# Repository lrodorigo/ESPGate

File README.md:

<p align="right">🇬🇧 English · <a href="README_IT.md">🇮🇹 Italiano</a></p>

<h1 align="center">⛩️ ESPGate v1.0</h1>

<h2 align="center">⏳ Built to last 10 years.<br>Isolated. Surge-protected. Local-first.</h2>

<p align="center"><b>Native ESPHome / Home Assistant 230V AC Gate &amp; Roller Shutter Controller</b></p>

<p align="center">
  <br>
  
</p>

> 💡 *Install it once. Forget it. Your gate just works—through thunderstorms, power surges and a decade of daily cycles.*

* 🧠 **Platform:** Custom `150 × 110 mm` PCB built around an `ESP32-S3-WROOM-1` for native ESPHome integration.
* ⚙️ **Target Load:** Single-phase `230V AC` sliding/swing gates (**single or double leaf**) and garage roller shutters.
* 🛡️ **Design Goal:** Industrial-grade mains isolation and surge protection in a single self-contained board—zero external relay modules or floating power supplies.
* ⚙️ **Motors:** up to `2×` single-phase `230V AC` motors (open/close), one per leaf.
* 📥 **Inputs:** opto-isolated `24V` (photocells, limit switches, push-buttons) plus a `433.92 MHz` rolling-code RF receiver (`4` channels).
* 📤 **Outputs:** motor phase + direction relays, a neutral relay per leaf, `230V AC` flashing beacon (SSR) and a free-contact auxiliary relay (`AUX`).

---

## 🤔 Why Yet Another Gate Controller?

* ❌ **The DIY Problem:** Cobbling consumer DIN-rail Wi-Fi relays with external `24V` PSUs and shared grounds leads to ESP32 brownouts, welded relay contacts, or fried GPIOs after the first thunderstorm.
* 🔒 **The Commercial Problem:** Traditional gate boards handle high voltage well, but trap you in proprietary remotes or clunky cloud bridges.
* ✅ **The ESPGate Solution:** Full galvanic isolation, dedicated surge protection, and hardware-interlocked relays paired with local-first ESPHome firmware.

> ⚠️ **HIGH VOLTAGE SAFETY WARNING**
> * Operates directly on lethal **230V AC mains voltage**. Always disconnect power at the main breaker before wiring or servicing.
> * Open-hardware DIY project without commercial CE certification—intended for experienced makers or installation by qualified personnel inside an IP56/IP65 enclosure.

---

## 📌 Project Status

> ### 🙋 Looking for expenses split!
> Help me get the first `5` boards made: **3 spots available at ~`55–60 €` each.**

* 🧪 **Stage:** Design updated with **double-leaf support** and an **RF receiver** (see [Changelog](#-changelog)), **not ordered yet**. Some sections below (renders, terminals, architecture) may still describe the previous single-leaf revision.
* 📦 **Batch:** The first prototype batch (PCB + SMT assembly from JLCPCB, `5` boards) is ready in the cart and will be ordered as soon as the 3 spare boards find a home.
* 🤝 **Looking for 3 early adopters:** I keep `2` boards for myself and I'm looking for `3` people willing to refund the cost of the other three boards (about `55–60 €` per board). Spending ~`300 €` for just two boards makes no sense, so splitting the batch is what makes this prototype run viable.
* 🛡️ **Risk is mine:** I will personally perform the **first power-up** and bring-up of every board. If a board doesn't work, that's on me, not on you.
* 📬 **Interested?** Open an issue or get in touch.

---

## 📝 Changelog

### Unreleased (since v1.0)

* ➕ **Double-leaf gate support:**
  * The `AUX` `triac` output was replaced with a `relay`, and an extra `relay` + `optocoupler` were added to drive a second leaf.
  * Both leaves share the same `MOTOR DIR` relay, so they always move in the direction set by how the phase is wired: leaf 1 clockwise / leaf 2 counter-clockwise (standard), or leaf 1 clockwise / leaf 2 clockwise.
  * The delay between the two leaves is **programmable**.
  * The direction wires of the two motors are wired **in parallel** (phase), while each leaf has its **own neutral relay**: leaf 1 uses the dedicated neutral relay (`GPIO15`), leaf 2 uses the `AUX` relay (`GPIO5`) with `AUX COM` wired to `N`.
* 📡 **RF remote receiver:**
  * Added a [`433.92 MHz` 4-channel rolling-code receiver module](https://rf-modules.com/433-92-Receiver-Module-with-on-board-decoding-RC-RHCS-4CH-p244180431) with on-board decoding.
  * `SMA` connector on the PCB for an external antenna.
  * The `4` RF channels are wired to independent ESP32 GPIOs, not in parallel with the push-buttons.
* 📍 **Pinout:** updated to the current schematic.

---

## 🏗️ System Architecture

---

## ✨ Key Hardware Features

* 🧠 **MCU & Debug:** `ESP32-S3-WROOM-1` with `FLASH`, `RESET`, and `CONFIG` tactile buttons, onboard UART header (`TX`/`RX`), and `STATUS` LED.
* 🔋 **Isolated Power:** Dual isolated Mean Well `IRM` AC/DC modules separating the `24V` field domain from the `3.3V` logic domain.
* ⚙️ **230V AC Motor Drive (`MOTOR`):**
  * Hardware-interlocked `AgSnO2` power relays (`MOTOR PWR` + `MOTOR DIR`) for Open/Close control (`AP` / `CH` / `COM`).
  * RC snubber networks across relay contacts to suppress inductive motor arcing.
* 🚨 **230V AC Auxiliary Outputs (`LAMP` / `AUX`):**
  * Opto-isolated Solid-State Relay (`BC2223A` SSR) for the flashing beacon (`LAMPEGGIANTE`).
  * `AUX` relay output for an auxiliary load (courtesy light / electric lock) or, with `AUX COM` wired to `N`, as the neutral relay of leaf 2.
* 🛡️ **Protection & Creepage:**
  * Dedicated `5×20 mm` replaceable fuses: `FH1` on the power supplies input, `FH3` on the motors, `FH4` on the `+24V` supply of photocells and inputs.
  * `14D471K` Metal Oxide Varistors (`MOV`) on AC mains input and output stages.
  * Physical PCB milling slots (`Edge.Cuts`) between `230V AC` and low-voltage sections.
* 🔌 **6× Opto-Isolated 24V Field Inputs (`LTV-847S`):**
  * Galvanically isolated inputs with onboard diagnostic LEDs (`P1`, `P2`, `L1`, `L2`, `B1`, `B2`):
    * **Photocells (`PHOTOC`):** `P1`, `P2`
    * **Limit Switches (`LIMIT SW`):** `L1` (Open), `L2` (Close)
    * **Push-Buttons (`BUTTONS`):** `B1` (Step-by-Step / Open), `B2` (Close / Pedestrian)
  * Dedicated `+24V` output terminals (`+24V INPUTS`) to power photocells and dry-contact switches.
* 📦 **Enclosure Fit:** Fits inside a standard **Gewiss GW44207** (`190 × 140 × 70 mm`) IP56 junction box via a 3D-printed adapter plate.

---

## 🔩 Terminal Block Overview

* 🔌 **J1 (`AC IN`):** `230V AC 50Hz` mains input (`L`, `N`, `PE`) protected by `FH1` (power supplies input) + `MOV`.
* ⚙️ **J2 (`MOTOR`):** `230V AC` single-phase motor output (`COM`, `OPEN`, `CLOSE`, `PE`) with hardware interlock and snubbers.
* 🚨 **J3 (`LAMP / AUX`):** `230V AC` SSR output for the flashing beacon (`LAMP`) and `AUX` relay output (leaf 2 neutral when `AUX COM` is wired to `N`).
* 🔋 **J4 (`+24V INPUTS`):** Isolated `24V DC` sensor supply (`-`, `-`, `+24`, `+24`).
* 👁️ **J5 (`PHOTOC`):** Opto-isolated photocell inputs (`C`, `1`, `2` → `P1`, `P2`).
* 🛑 **J6 (`LIMIT SW`):** Opto-isolated open/close limit switch inputs (`C`, `1`, `2` → `L1`, `L2`).
* 🔘 **J7 (`BUTTONS`):** Opto-isolated wall push-button inputs (`C`, `1`, `2` → `B1`, `B2`).

---
## 📍 ESP32-S3 Pinout Map

* 📤 **Outputs:**
  * `GPIO16` (`ESP_REL_MOT_PWR`, Active `HIGH`): Motor phase activation relay (`MOTOR PWR`).
  * `GPIO7` (`ESP_REL_DIR`, Active `HIGH`): Direction relay (`MOTOR DIR`), shared by both leaves.
  * `GPIO15` (`ESP_N_MOT1`, Active `HIGH`): Neutral relay of motor 1 / leaf 1.
  * `GPIO6` (`ESP_LAMP`, Active `HIGH`): Flashing beacon SSR (`LAMP`).
  * `GPIO5` (`ESP_AUX`, Active `HIGH`): `AUX` relay, used as the neutral relay of leaf 2 when `AUX COM` is wired to `N`.
  * `GPIO4` (`ESP_LED_GR`, Active `HIGH`): Onboard green status LED (`STATUS`).
* 📥 **Inputs:**
  * `GPIO9` (`ESP_IN_FOTOC_1`, Active `LOW`): Photocell 1 (`P1`).
  * `GPIO10` (`ESP_IN_FOTOC_2`, Active `LOW`): Photocell 2 (`P2`).
  * `GPIO12` (`ESP_IN_LIMIT_1`, Active `LOW`): Limit switch 1 (`L1`).
  * `GPIO11` (`ESP_IN_LIMIT_2`, Active `LOW`): Limit switch 2 (`L2`).
  * `GPIO38` (`ESP_IN_BTN_1`, Active `LOW`): Push-button 1 (`B1`).
  * `GPIO39` (`ESP_IN_BTN_2`, Active `LOW`): Push-button 2 (`B2`).
  * `GPIO13` (`SW3`, Active `LOW`): Onboard `CONFIG` button.
* 📡 **RF Receiver (`J9`, `4` independent channels, not in parallel with the buttons):**
  * `GPIO14` (`RF_CH1`), `GPIO21` (`RF_CH2`), `GPIO40` (`RF_CH3`), `GPIO41` (`RF_CH4`), each with a `10 kΩ` pull-up to `3.3V`.
* 🔌 **Debug UART (`J4`):**
  * `GPIO0` (`SW1`, Active `LOW`): Onboard `FLASH` / Boot mode button.
  * `GPIO43` (`TXD0`) / `GPIO44` (`RXD0`): 3.3V UART header (`330 Ω` series protection resistors).

---

## 🚀 Quick Start (ESPHome)

* **1. Flash:** Connect a `3.3V` USB-to-UART adapter to the `ESP` header (`+`, `-`, `RX`, `TX`), hold `FLASH`, and press `RESET`.
* **2. Configure:** Load the ESPHome YAML configuration, set `secrets.yaml` (Wi-Fi + API key), and tune `open_duration` / `close_duration`.
* **3. Bench Test:** Verify limit switches (`L1`, `L2`) and photocells (`P1`, `P2`) via onboard diagnostic LEDs before connecting `230V AC` motor leads.

---

## 📜 Disclaimer & License

* **License:** CERN Open Hardware Licence v2 - Permissive (`CERN-OHL-P`) / `MIT`.
* **Liability:** Provided as-is for educational and DIY purposes; the author assumes no liability for personal injury, property damage, or regulatory compliance.

---

## 📐 Mechanical

* 🔩 **Mounting:** Secured by `4×` **M4** screws, one in each corner.
* 📏 **Board Size:** `150 × 111 mm`, mounting holes on a `138 × 100 mm` grid.

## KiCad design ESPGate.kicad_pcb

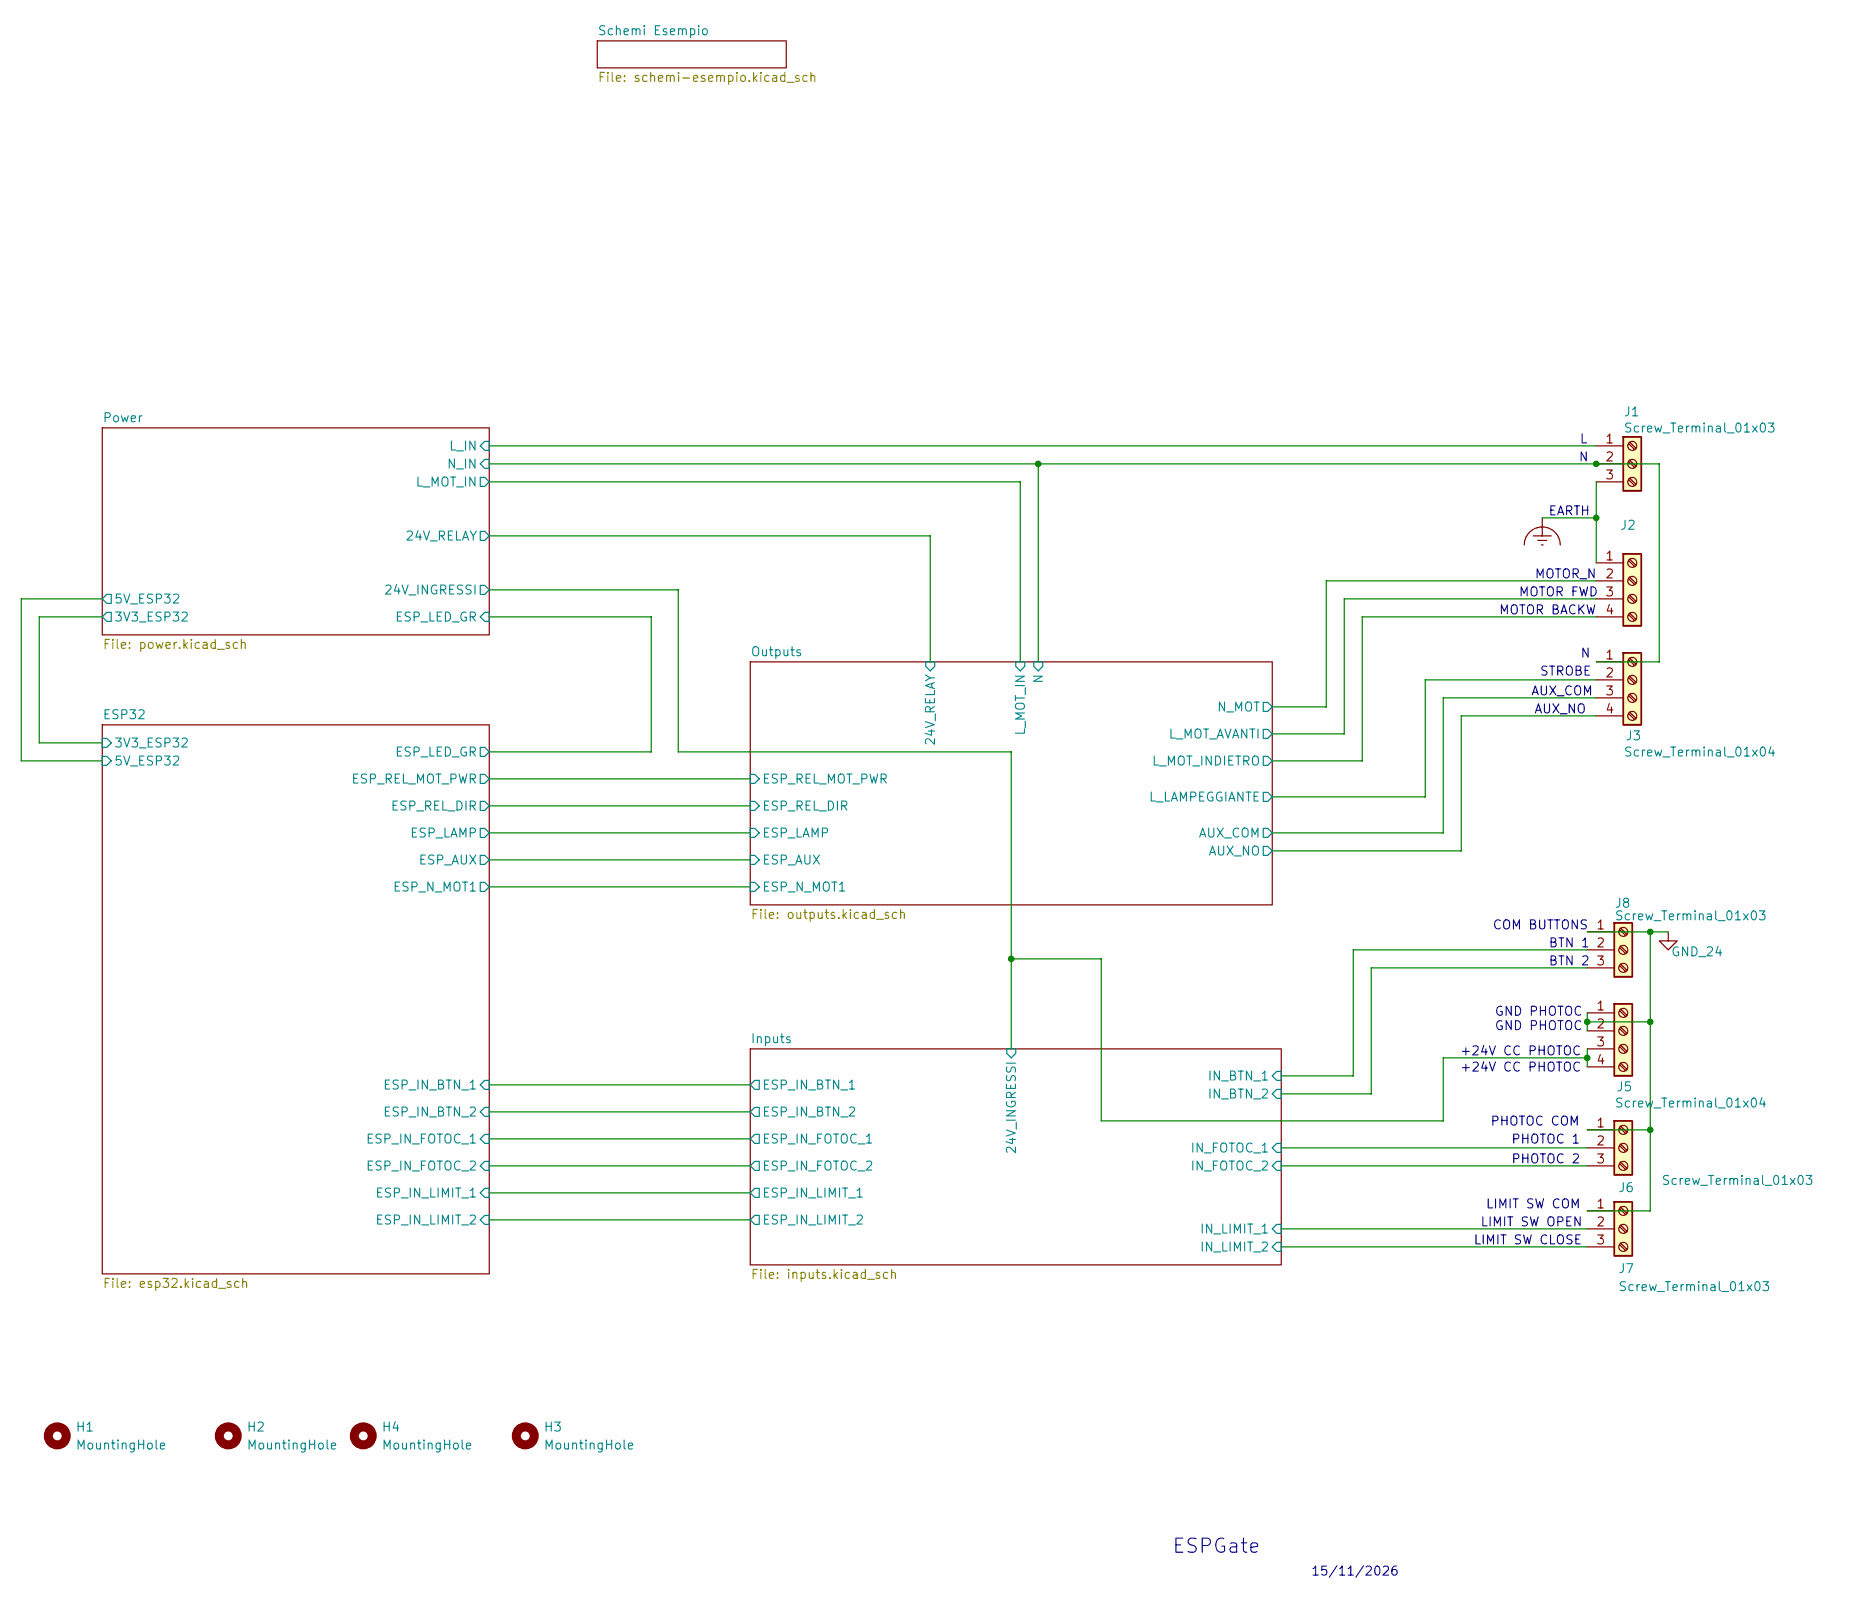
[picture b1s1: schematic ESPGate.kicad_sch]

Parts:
H1, H2, H3, H4: MountingHole; MountingHole_4.3mm_M4_DIN965
J1, J6, J7, J8: Screw_Terminal_01x03; CONN-TH_3P-P5.00_WJ500V-5.08-3P
J2, J3, J5: Screw_Terminal_01x04; CONN-TH_4P-P5.08_DIBO_DB128V-5.08

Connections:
24V_INGRESSI: J5.3, J5.4; also elsewhere on the board
/Inputs/IN_BTN_1: J8.2; also elsewhere on the board
/Inputs/IN_BTN_2: J8.3; also elsewhere on the board
/Inputs/IN_FOTOC_1: J6.2; also elsewhere on the board
/Inputs/IN_FOTOC_2: J6.3; also elsewhere on the board
/Inputs/IN_LIMIT_1: J7.2; also elsewhere on the board
/Inputs/IN_LIMIT_2: J7.3; also elsewhere on the board
/Outputs/AUX_COM: J3.3; also elsewhere on the board
/Outputs/AUX_NO: J3.4; also elsewhere on the board
/Outputs/L_LAMPEGGIANTE: J3.2; also elsewhere on the board
/Outputs/L_MOT_AVANTI: J2.3; also elsewhere on the board
/Outputs/L_MOT_INDIETRO: J2.4; also elsewhere on the board
/Outputs/N: J1.2, J3.1; also elsewhere on the board
/Outputs/N_MOT: J2.2; also elsewhere on the board
/Power/L_IN: J1.1; also elsewhere on the board
Earth_Clean: J1.3, J2.1
GND_24: J5.1, J5.2, J6.1, J7.1, J8.1; also elsewhere on the board

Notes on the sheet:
BTN 2
15/11/2026
+24V CC PHOTOC
AUX_NO
GND PHOTOC
PHOTOC COM
STROBE
ESPGate
LIMIT SW OPEN
LIMIT SW COM
PHOTOC 2
MOTOR BACKW
BTN 1
MOTOR_N
PHOTOC 1
EARTH
LIMIT SW CLOSE
MOTOR FWD
COM BUTTONS
AUX_COM

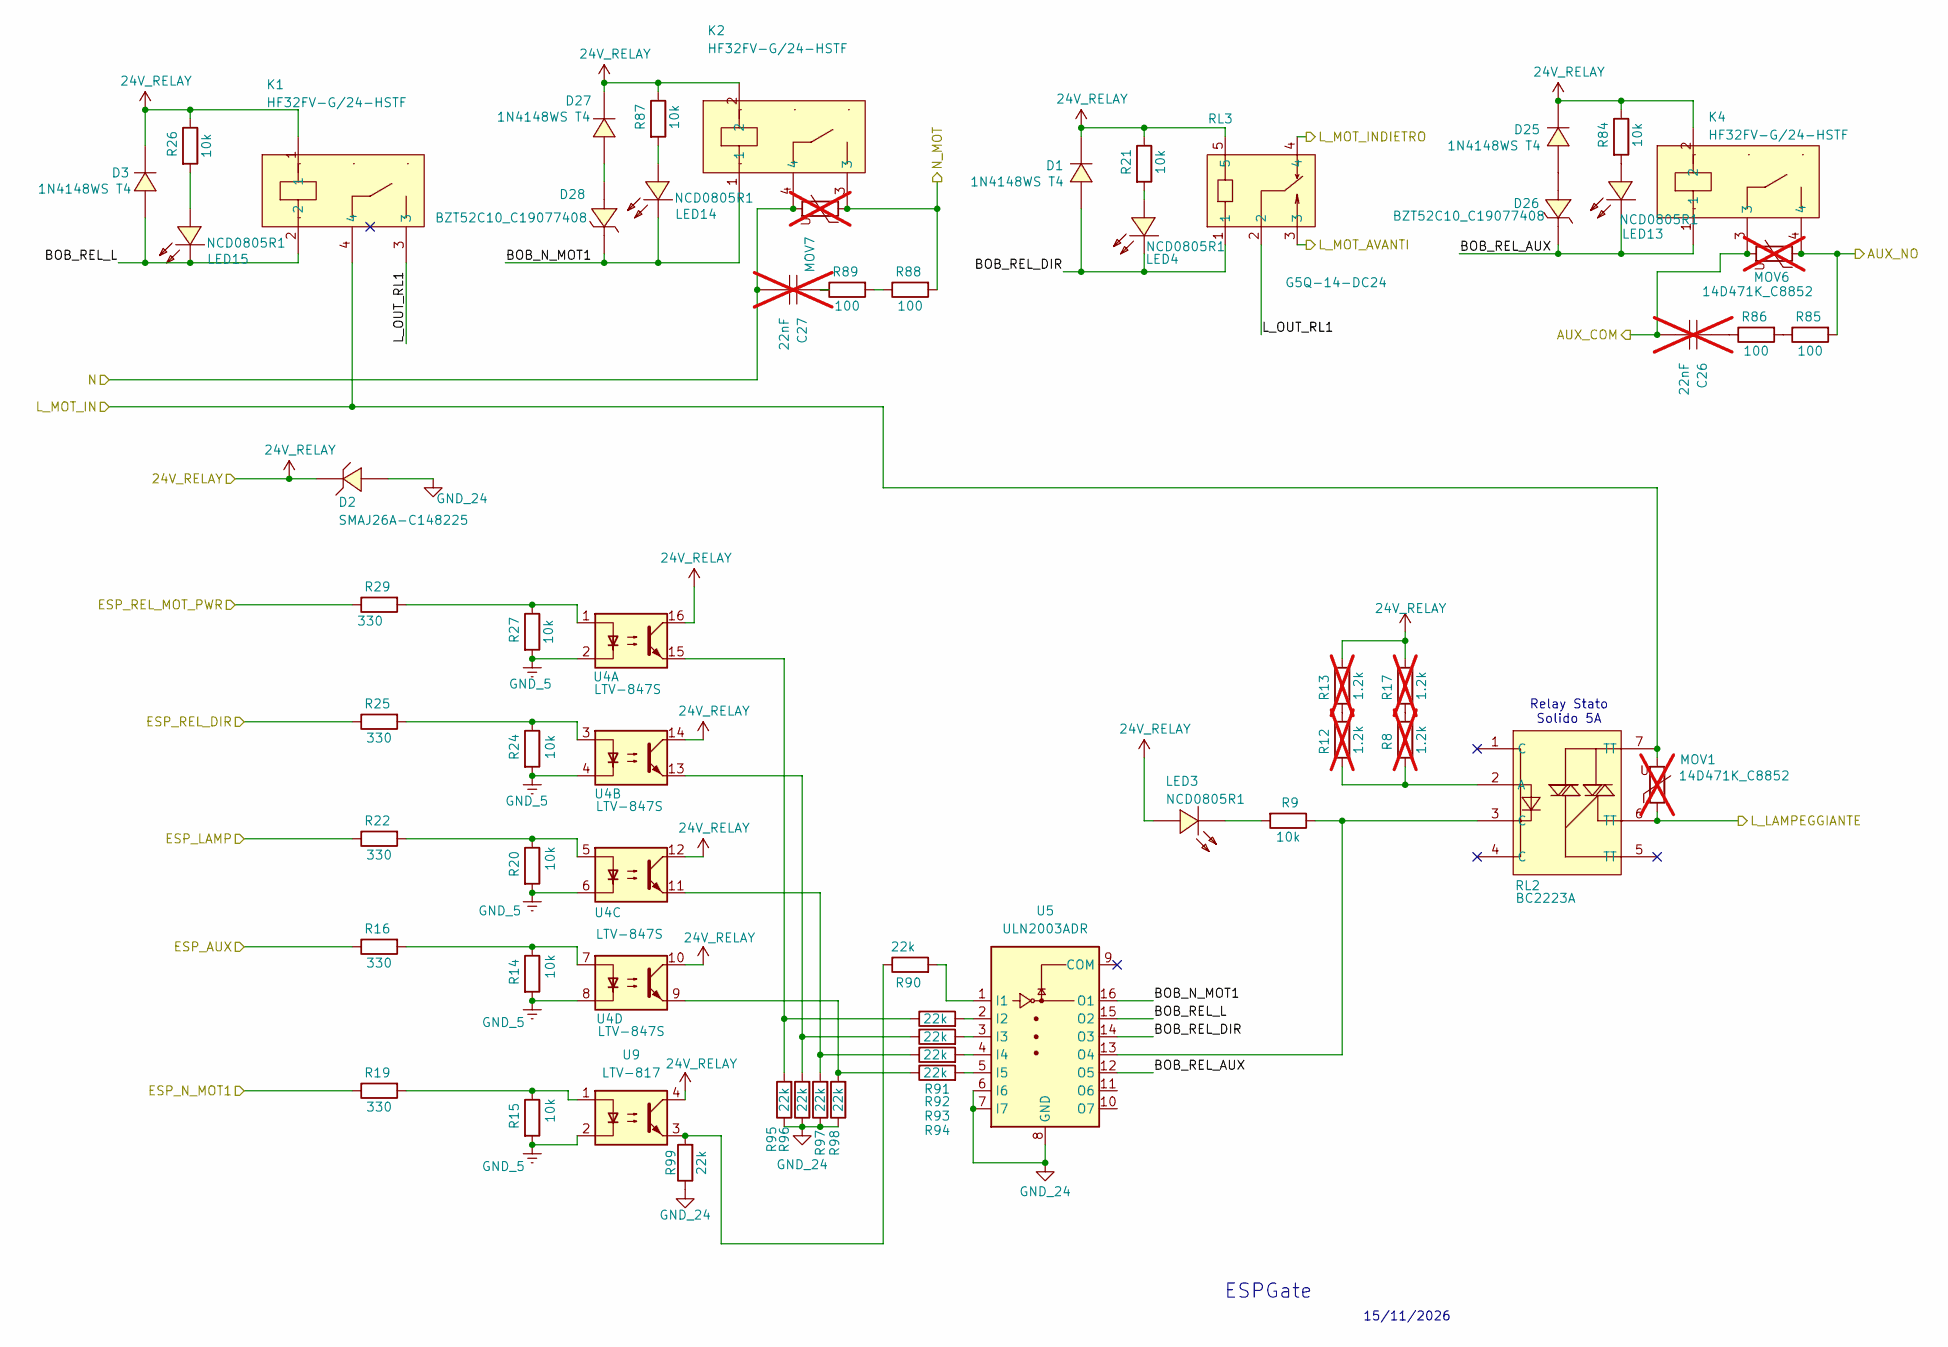
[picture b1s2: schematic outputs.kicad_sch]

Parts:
C26, C27: 22nF; CAP-TH_L13.0-W5.0-P10.00-D0.6; LCSC Part C390050; not fitted
D1, D3, D25, D27: 1N4148WS T4; SOD-323_L1.8-W1.3-LS2.5-RD; LCSC Part C2128
D2: SMAJ26A-C148225; SMA_L4.4-W2.6-LS5.0-RD; LCSC Part C148225
D26, D28: BZT52C10_C19077408; SOD-123_L2.7-W1.6-LS3.7-RD; LCSC Part C19077408
K1, K2, K4: HF32FV-G/24-HSTF; RELAY-TH_HF32FV-G; LCSC Part C194243
LED3, LED4, LED13, LED14, LED15: NCD0805R1; LED0805-R-RD; LCSC Part C84256
MOV1, MOV6, MOV7: 14D471K_C8852; RES-TH_L16.5-W5.9-P7.50-D0.8-S3.00; LCSC Part C8852; not fitted
R8, R12, R13, R17: 1.2k; R0805; LCSC Part C17379; not fitted
R9, R14, R15, R20, R21, R24, R26, R27, R84, R87: 10k; R0805; LCSC Part C17414
R16, R19, R22, R25, R29: 330; R0805; LCSC Part C17630
R85, R86, R88, R89: 100; R1206; LCSC Part C17901
R90, R91, R92, R93, R94, R95, R96, R97, R98, R99: 22k; R0603; LCSC Part C31850
RL2: BC2223A; SMD-8_7P-L9.7-W6.4-P2.54-LS10.0-BL; LCSC Part C596513
RL3: G5Q-14-DC24; RELAY-TH_G5Q-14-DCXX; LCSC Part C397242
U4: LTV-847S; SMDIP-16_W9.53mm; LCSC Part C114599
U5: ULN2003ADR; SOIC-16_L9.9-W3.9-P1.27-LS6.0-BL; LCSC Part C7512
U9: LTV-817; OPTO-SMD-4_L4.6-W6.5-P2.54-LS10.3-BL; LCSC Part C109227

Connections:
24V_RELAY: D1.1 (K), D2.1 (C), D3.1 (K), D25.1 (K), D27.1 (K), K1.1, K2.2, K4.2, LED3.1 (+), R13.2, R17.2, R21.1, R26.1, R84.1, R87.1, RL3.5, U4.10, U4.12, U4.14, U4.16, U9.4; also elsewhere on the board
/ESP32/ESP_AUX: R16.1; also elsewhere on the board
/ESP32/ESP_LAMP: R22.1; also elsewhere on the board
/ESP32/ESP_N_MOT1: R19.1; also elsewhere on the board
/ESP32/ESP_REL_DIR: R25.1; also elsewhere on the board
/ESP32/ESP_REL_MOT_PWR: R29.1; also elsewhere on the board
/Outputs/AUX_COM: C26.1, K4.3, MOV6.2; also elsewhere on the board
/Outputs/AUX_NO: K4.4, MOV6.1, R85.2; also elsewhere on the board
/Outputs/BOB_N_MOT1: D28.1 (K), K2.1, LED14.2 (-), U5.16 (O1)
/Outputs/BOB_REL_AUX: D26.1 (K), K4.1, LED13.2 (-), U5.12 (O5)
/Outputs/BOB_REL_DIR: D1.2 (A), LED4.2 (-), RL3.1, U5.14 (O3)
/Outputs/BOB_REL_L: D3.2 (A), K1.2, LED15.2 (-), U5.15 (O2)
/Outputs/L_LAMPEGGIANTE: MOV1.1, RL2.6 (TT); also elsewhere on the board
/Outputs/L_MOT_AVANTI: RL3.3; also elsewhere on the board
/Outputs/L_MOT_IN: K1.4, MOV1.2, RL2.7 (TT); also elsewhere on the board
/Outputs/L_MOT_INDIETRO: RL3.4; also elsewhere on the board
/Outputs/L_OUT_RL1: K1.3, RL3.2
/Outputs/N: C27.1, K2.4, MOV7.2; also elsewhere on the board
/Outputs/N_MOT: K2.3, MOV7.1, R88.2; also elsewhere on the board
GND_5: R14.2, R15.2, R20.2, R24.2, R27.2, U4.2, U4.4, U4.6, U4.8, U9.2; also elsewhere on the board
GND_24: D2.2 (A), R95.1, R96.1, R97.1, R98.1, R99.1, U5.6 (I6), U5.7 (I7), U5.8 (GND); also elsewhere on the board
unnamed: C26.2, R86.1
unnamed: C27.2, R89.1
unnamed: D25.2 (A), D26.2 (A)
unnamed: D27.2 (A), D28.2 (A)
unnamed: LED3.2 (-), R9.2
unnamed: LED4.1 (+), R21.2
unnamed: LED13.1 (+), R84.2
unnamed: LED14.1 (+), R87.2
unnamed: LED15.1 (+), R26.2
unnamed: R12.2, R13.1
unnamed: R14.1, R16.2, U4.7
unnamed: R15.1, R19.2, U9.1
unnamed: R8.2, R17.1
unnamed: R20.1, R22.2, U4.5
unnamed: R24.1, R25.2, U4.3
unnamed: R27.1, R29.2, U4.1
unnamed: R85.1, R86.2
unnamed: R88.1, R89.2
unnamed: R90.1, R99.2, U9.3
unnamed: R91.1, R95.2, U4.15
unnamed: R92.1, R96.2, U4.13
unnamed: R93.1, R97.2, U4.11
unnamed: R94.1, R98.2, U4.9
unnamed: R8.1, R12.1, RL2.2 (A)
unnamed: R90.2, U5.1 (I1)
unnamed: R91.2, U5.2 (I2)
unnamed: R92.2, U5.3 (I3)
unnamed: R93.2, U5.4 (I4)
unnamed: R94.2, U5.5 (I5)
unnamed: R9.1, RL2.3 (C), U5.13 (O4)

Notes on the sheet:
ESPGate
15/11/2026
Relay Stato Solido 5A

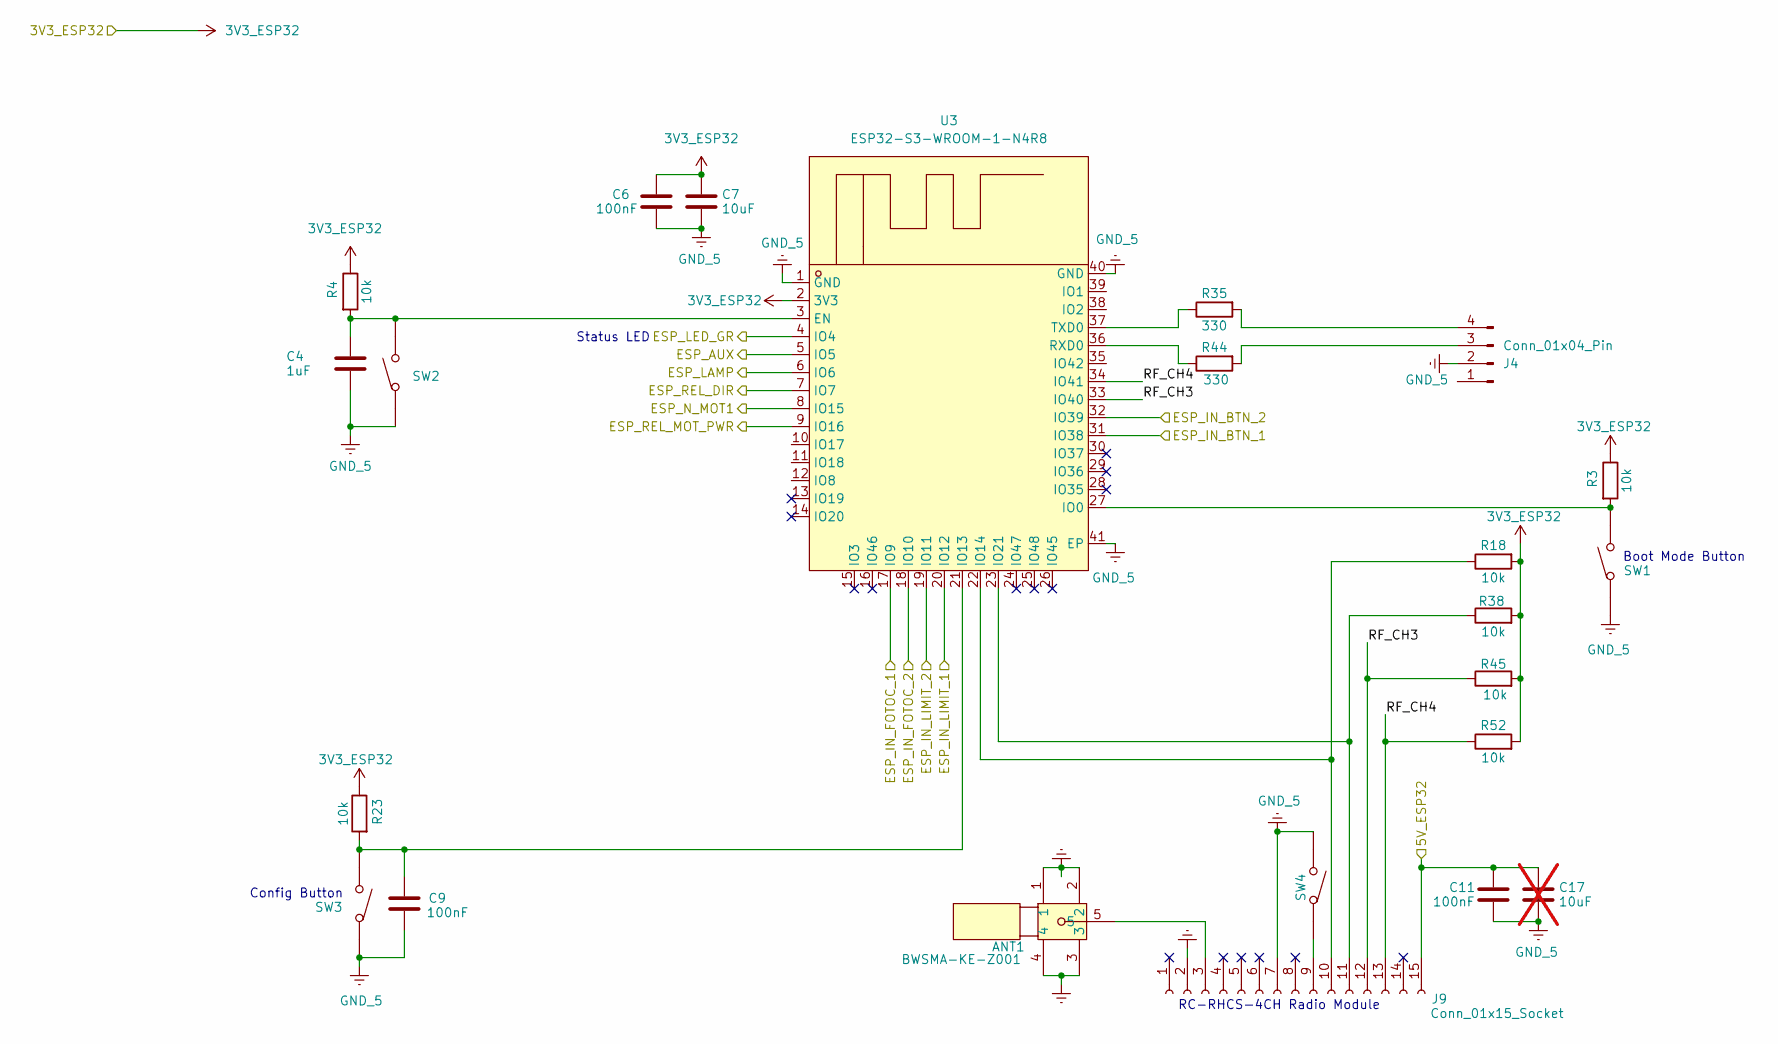
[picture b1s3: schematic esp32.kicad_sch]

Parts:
ANT1: BWSMA-KE-Z001; SMA-TH_BWSMA-KE-Z001; LCSC Part C496549
C4: 1uF; C0805; LCSC Part C28323
C6, C9, C11: 100nF; C0805; LCSC Part C28233
C7: 10uF; C0603; LCSC Part C19702
C17: 10uF; C0603; LCSC Part C19702; not fitted
J4: Conn_01x04_Pin; PinHeader_1x04_P2.54mm_Vertical
J9: Conn_01x15_Socket; RC-RHCS-4CH
R3, R4, R18, R23, R38, R45, R52: 10k; R0805; LCSC Part C17414
R35, R44: 330; R0805; LCSC Part C17630
SW1, SW2, SW3, SW4: TS-1088-AR02016; SW-SMD_L3.9-W3.0-P4.45; LCSC Part C720477
U3: ESP32-S3-WROOM-1-N4R8; WIFIM-SMD_ESP32-S3-WROOM-1-N8; LCSC Part C2913200

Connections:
3V3_ESP32: C6.1, C7.1, R3.1, R4.1, R18.2, R23.1, R38.2, R45.2, R52.2, U3.2 (3V3); also elsewhere on the board
/ESP32/ESP_AUX: U3.5 (IO5); also elsewhere on the board
/ESP32/ESP_IN_BTN_1: U3.31 (IO38); also elsewhere on the board
/ESP32/ESP_IN_BTN_2: U3.32 (IO39); also elsewhere on the board
/ESP32/ESP_IN_FOTOC_1: U3.17 (IO9); also elsewhere on the board
/ESP32/ESP_IN_FOTOC_2: U3.18 (IO10); also elsewhere on the board
/ESP32/ESP_IN_LIMIT_1: U3.20 (IO12); also elsewhere on the board
/ESP32/ESP_IN_LIMIT_2: U3.19 (IO11); also elsewhere on the board
/ESP32/ESP_LAMP: U3.6 (IO6); also elsewhere on the board
/ESP32/ESP_LED_GR: U3.4 (IO4); also elsewhere on the board
/ESP32/ESP_N_MOT1: U3.8 (IO15); also elsewhere on the board
/ESP32/ESP_REL_DIR: U3.7 (IO7); also elsewhere on the board
/ESP32/ESP_REL_MOT_PWR: U3.9 (IO16); also elsewhere on the board
/ESP32/RF_CH3: J9.12, R45.1, U3.33 (IO40)
/ESP32/RF_CH4: J9.13, R52.1, U3.34 (IO41)
/Power/5V_ESP32: C11.1, C17.1, J9.15; also elsewhere on the board
GND_5: ANT1.1, ANT1.2, ANT1.3, ANT1.4, C4.2, C6.2, C7.2, C9.2, C11.2, C17.2, J4.2, J9.2, J9.7, SW1.1, SW2.1, SW3.1, SW4.2, U3.1 (GND), U3.40 (GND), U3.41 (EP); also elsewhere on the board
unnamed: J4.3, R44.2
unnamed: J4.4, R35.2
unnamed: ANT1.5, J9.3
unnamed: J9.9, SW4.1
unnamed: J9.10, R18.1, U3.22 (IO14)
unnamed: J9.11, R38.1, U3.23 (IO21)
unnamed: C4.1, R4.2, SW2.2, U3.3 (EN)
unnamed: R3.2, SW1.2, U3.27 (IO0)
unnamed: C9.1, R23.2, SW3.2, U3.21 (IO13)
unnamed: R44.1, U3.36 (RXD0)
unnamed: R35.1, U3.37 (TXD0)

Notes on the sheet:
RC-RHCS-4CH Radio Module
Boot Mode Button
Status LED
Config Button

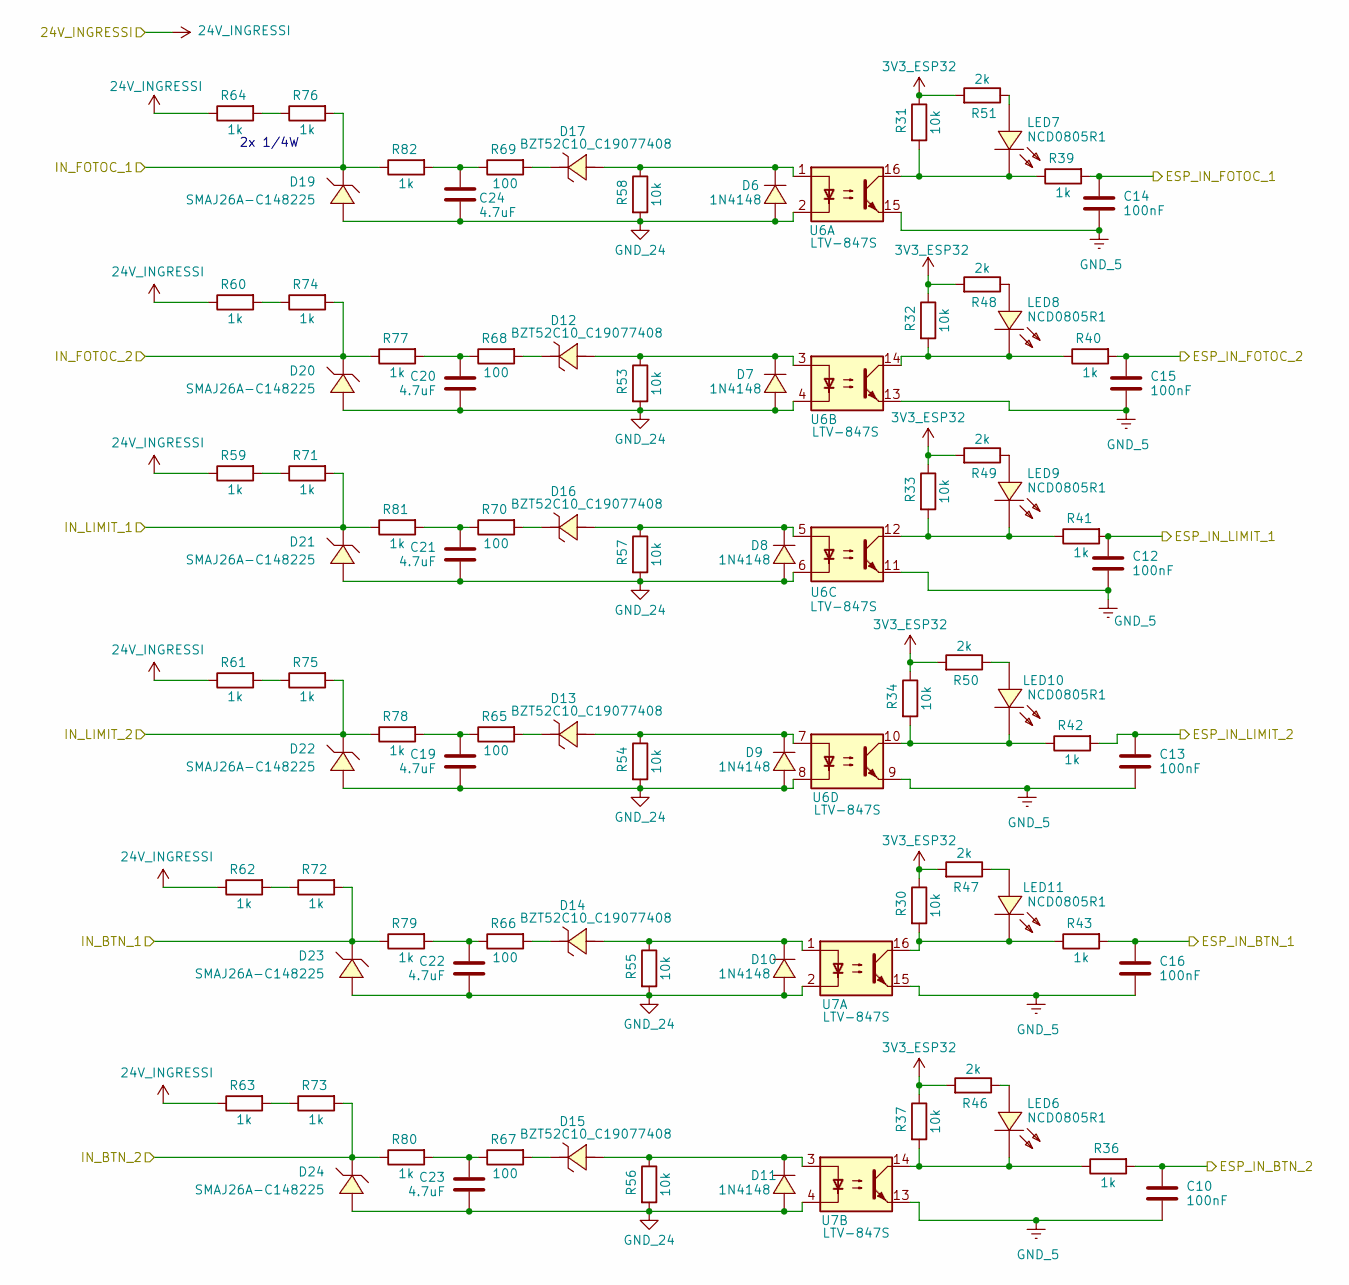
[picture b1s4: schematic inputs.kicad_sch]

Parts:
C10, C12, C13, C14, C15, C16: 100nF; C0805; LCSC Part C28233
C19, C20, C21, C22, C23, C24: 4.7uF; C0805; LCSC Part C1779
D6, D7, D8, D9, D10, D11: 1N4148; SOD-323_L1.8-W1.3-LS2.5-RD; LCSC Part C2128
D12, D13, D14, D15, D16, D17: BZT52C10_C19077408; SOD-123_L2.7-W1.6-LS3.7-RD; LCSC Part C19077408
D19, D20, D21, D22, D23, D24: SMAJ26A-C148225; SMA_L4.4-W2.6-LS5.0-RD; LCSC Part C148225
LED6, LED7, LED8, LED9, LED10, LED11: NCD0805R1; LED0805-R-RD; LCSC Part C84256
R30, R31, R32, R33, R34, R37, R53, R54, R55, R56, R57, R58: 10k; R0805; LCSC Part C17414
R36, R39, R40, R41, R42, R43, R77, R78, R79, R80, R81, R82: 1k; R0805; LCSC Part C17513
R46, R47, R48, R49, R50, R51: 2k; R0805; LCSC Part C17604
R59, R60, R61, R62, R63, R64, R71, R72, R73, R74, R75, R76: 1k; R1206; LCSC Part C4410
R65, R66, R67, R68, R69, R70: 100; R0805; LCSC Part C17408
U6, U7: LTV-847S; SMDIP-16_W9.53mm; LCSC Part C114599

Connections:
3V3_ESP32: R30.1, R31.1, R32.1, R33.1, R34.1, R37.1, R46.2, R47.2, R48.2, R49.2, R50.2, R51.2; also elsewhere on the board
24V_INGRESSI: R59.1, R60.1, R61.1, R62.1, R63.1, R64.1; also elsewhere on the board
/ESP32/ESP_IN_BTN_1: C16.1, R43.2; also elsewhere on the board
/ESP32/ESP_IN_BTN_2: C10.1, R36.2; also elsewhere on the board
/ESP32/ESP_IN_FOTOC_1: C14.1, R39.2; also elsewhere on the board
/ESP32/ESP_IN_FOTOC_2: C15.1, R40.2; also elsewhere on the board
/ESP32/ESP_IN_LIMIT_1: C12.1, R41.2; also elsewhere on the board
/ESP32/ESP_IN_LIMIT_2: C13.1, R42.2; also elsewhere on the board
/Inputs/IN_BTN_1: D23.1 (C), R72.2, R79.1; also elsewhere on the board
/Inputs/IN_BTN_2: D24.1 (C), R73.2, R80.1; also elsewhere on the board
/Inputs/IN_FOTOC_1: D19.1 (C), R76.2, R82.1; also elsewhere on the board
/Inputs/IN_FOTOC_2: D20.1 (C), R74.2, R77.1; also elsewhere on the board
/Inputs/IN_LIMIT_1: D21.1 (C), R71.2, R81.1; also elsewhere on the board
/Inputs/IN_LIMIT_2: D22.1 (C), R75.2, R78.1; also elsewhere on the board
GND_5: C10.2, C12.2, C13.2, C14.2, C15.2, C16.2, U6.9, U6.11, U6.13, U6.15, U7.13, U7.15; also elsewhere on the board
GND_24: C19.2, C20.2, C21.2, C22.2, C23.2, C24.2, D6.2 (A), D7.2 (A), D8.2 (A), D9.2 (A), D10.2 (A), D11.2 (A), D19.2 (A), D20.2 (A), D21.2 (A), D22.2 (A), D23.2 (A), D24.2 (A), R53.2, R54.2, R55.2, R56.2, R57.2, R58.2, U6.2, U6.4, U6.6, U6.8, U7.2, U7.4; also elsewhere on the board
unnamed: C19.1, R65.1, R78.2
unnamed: C20.1, R68.1, R77.2
unnamed: C21.1, R70.1, R81.2
unnamed: C22.1, R66.1, R79.2
unnamed: C23.1, R67.1, R80.2
unnamed: C24.1, R69.1, R82.2
unnamed: D10.1 (K), D14.2 (A), R55.1, U7.1
unnamed: D11.1 (K), D15.2 (A), R56.1, U7.3
unnamed: D7.1 (K), D12.2 (A), R53.1, U6.3
unnamed: D12.1 (K), R68.2
unnamed: D9.1 (K), D13.2 (A), R54.1, U6.7
unnamed: D13.1 (K), R65.2
unnamed: D14.1 (K), R66.2
unnamed: D15.1 (K), R67.2
unnamed: D8.1 (K), D16.2 (A), R57.1, U6.5
unnamed: D16.1 (K), R70.2
unnamed: D6.1 (K), D17.2 (A), R58.1, U6.1
unnamed: D17.1 (K), R69.2
unnamed: LED6.1 (+), R46.1
unnamed: LED6.2 (-), R36.1, R37.2, U7.14
unnamed: LED7.1 (+), R51.1
unnamed: LED7.2 (-), R31.2, R39.1, U6.16
unnamed: LED8.1 (+), R48.1
unnamed: LED8.2 (-), R32.2, R40.1, U6.14
unnamed: LED9.1 (+), R49.1
unnamed: LED9.2 (-), R33.2, R41.1, U6.12
unnamed: LED10.1 (+), R50.1
unnamed: LED10.2 (-), R34.2, R42.1, U6.10
unnamed: LED11.1 (+), R47.1
unnamed: LED11.2 (-), R30.2, R43.1, U7.16
unnamed: R59.2, R71.1
unnamed: R60.2, R74.1
unnamed: R61.2, R75.1
unnamed: R62.2, R72.1
unnamed: R63.2, R73.1
unnamed: R64.2, R76.1

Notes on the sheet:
2x 1/4W

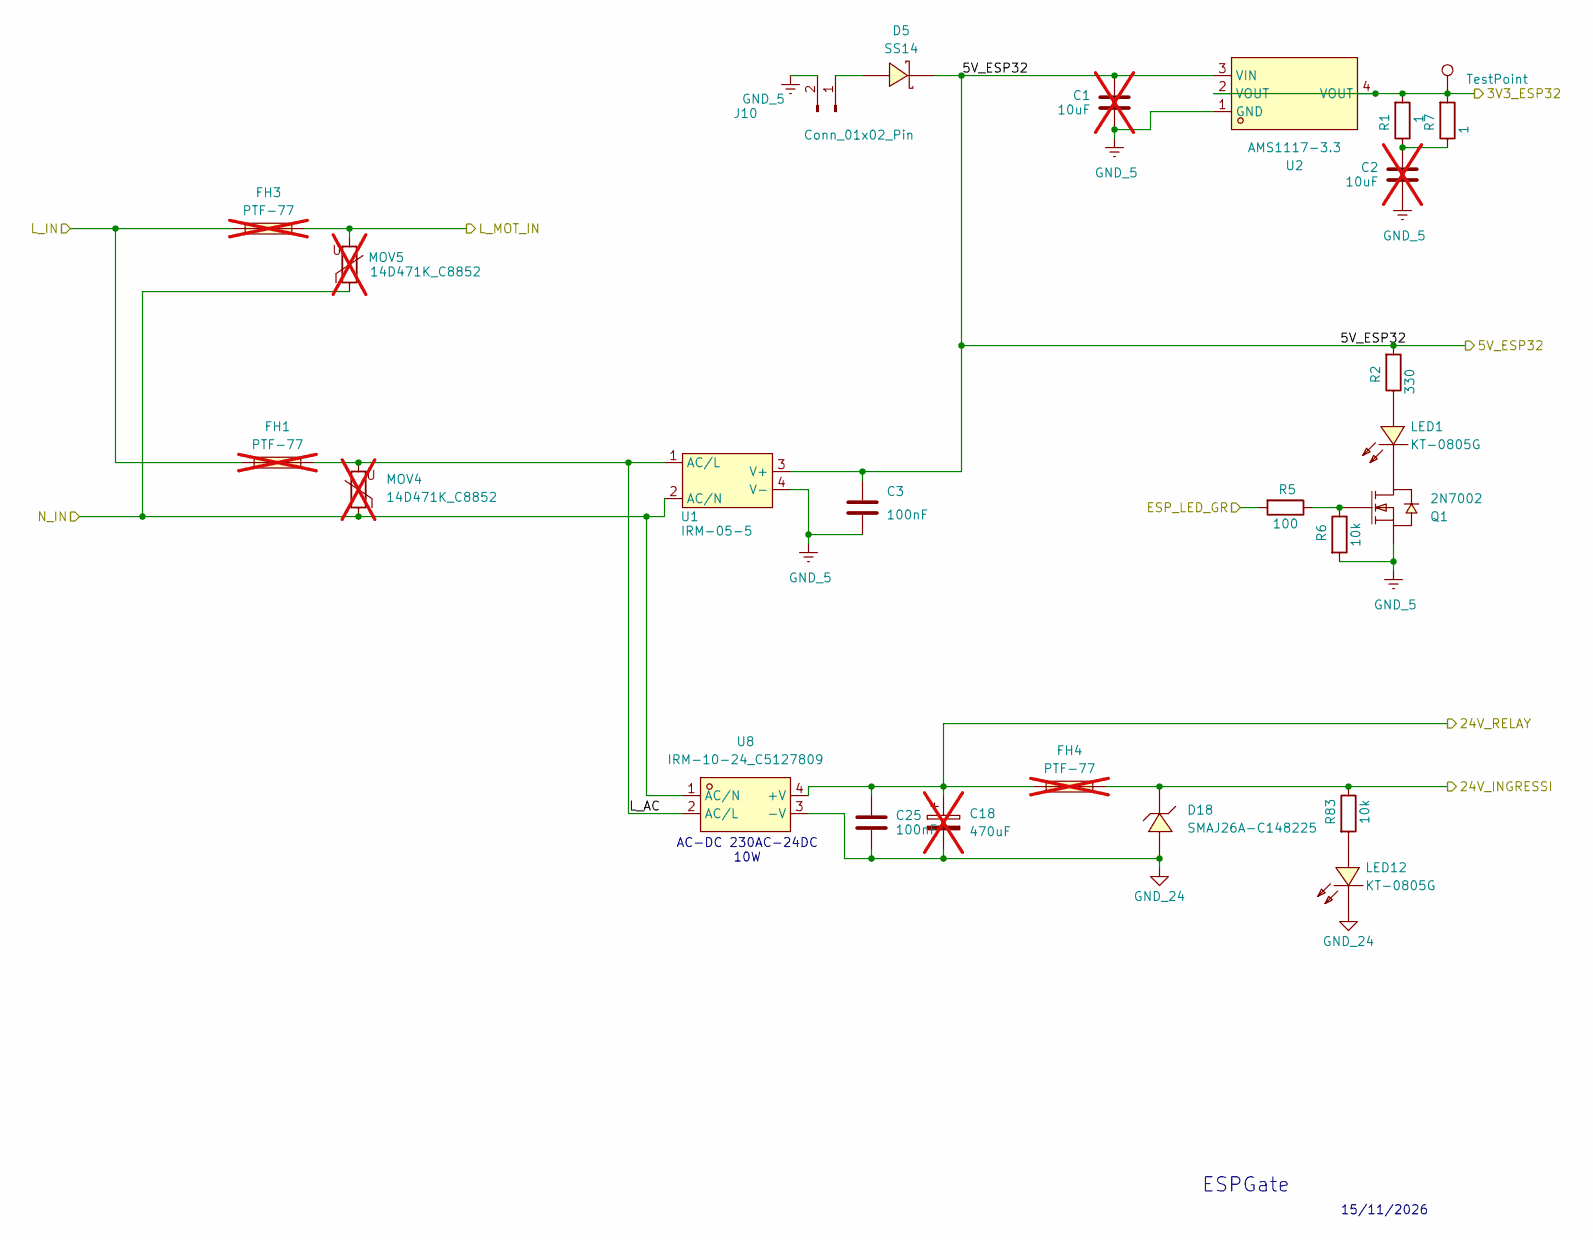
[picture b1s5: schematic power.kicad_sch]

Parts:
C1, C2: 10uF; C0603; LCSC Part C19702; not fitted
C3, C25: 100nF; C0805; LCSC Part C28233
C18: 470uF; CP_Radial_D10.0mm_P5.00mm; not fitted
D5: SS14; SMA_L4.2-W2.6-LS5.0-RD_1; LCSC Part C2480
D18: SMAJ26A-C148225; SMA_L4.4-W2.6-LS5.0-RD; LCSC Part C148225
FH1, FH3, FH4: PTF-77; FUSE-TH_L24.4-W9.4-P22.60; LCSC Part C717030; not fitted
J10: Conn_01x02_Pin; PinHeader_1x02_P2.54mm_Vertical
LED1, LED12: KT-0805G; LED0805-R-RD; LCSC Part C2297
MOV4, MOV5: 14D471K_C8852; RES-TH_L16.5-W5.9-P7.50-D0.8-S3.00; LCSC Part C8852; not fitted
Q1: 2N7002; SOT-23-3_L2.9-W1.3-P1.90-LS2.4-BR; LCSC Part C8545
R1, R7: 1; R0805; LCSC Part C25271
R2: 330; R0805; LCSC Part C17630
R5: 100; R1206; LCSC Part C17901
R6, R83: 10k; R0805; LCSC Part C17414
TP3: TestPoint
U1: IRM-05-5; PWRM-TH_IRM-05-5; LCSC Part C48603696
U2: AMS1117-3.3; SOT-223-3_L6.5-W3.4-P2.30-LS7.0-BR; LCSC Part C6186
U8: IRM-10-24_C5127809; PWRM-TH_4P-L45.7-W25.4-P8.0; LCSC Part C5127809

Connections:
3V3_ESP32: R1.2, R7.2, TP3.1, U2.2 (VOUT), U2.4 (VOUT); also elsewhere on the board
24V_INGRESSI: D18.1 (C), FH4.2, R83.1; also elsewhere on the board
24V_RELAY: C18.1, C25.1, FH4.1, U8.4 (+V); also elsewhere on the board
/ESP32/ESP_LED_GR: R5.2; also elsewhere on the board
/Outputs/L_MOT_IN: FH3.1, MOV5.2; also elsewhere on the board
/Outputs/N: MOV4.1, MOV5.1, U1.2 (AC/N), U8.1 (AC/N); also elsewhere on the board
/Power/5V_ESP32: C1.1, C3.1, D5.1 (K), R2.2, U1.3 (V+), U2.3 (VIN); also elsewhere on the board
/Power/L_AC: FH1.2, MOV4.2, U1.1 (AC/L), U8.2 (AC/L)
/Power/L_IN: FH1.1, FH3.2; also elsewhere on the board
GND_5: C1.2, C2.2, C3.2, J10.2, Q1.2 (S), R6.2, U1.4 (V-), U2.1 (GND); also elsewhere on the board
GND_24: C18.2, C25.2, D18.2 (A), LED12.2 (-), U8.3 (-V); also elsewhere on the board
unnamed: C2.1, R1.1, R7.1
unnamed: D5.2 (A), J10.1
unnamed: LED1.1 (+), R2.1
unnamed: LED1.2 (-), Q1.3 (D)
unnamed: LED12.1 (+), R83.2
unnamed: Q1.1 (G), R5.1, R6.1

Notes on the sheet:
ESPGate
15/11/2026
AC-DC 230AC-24DC 10W

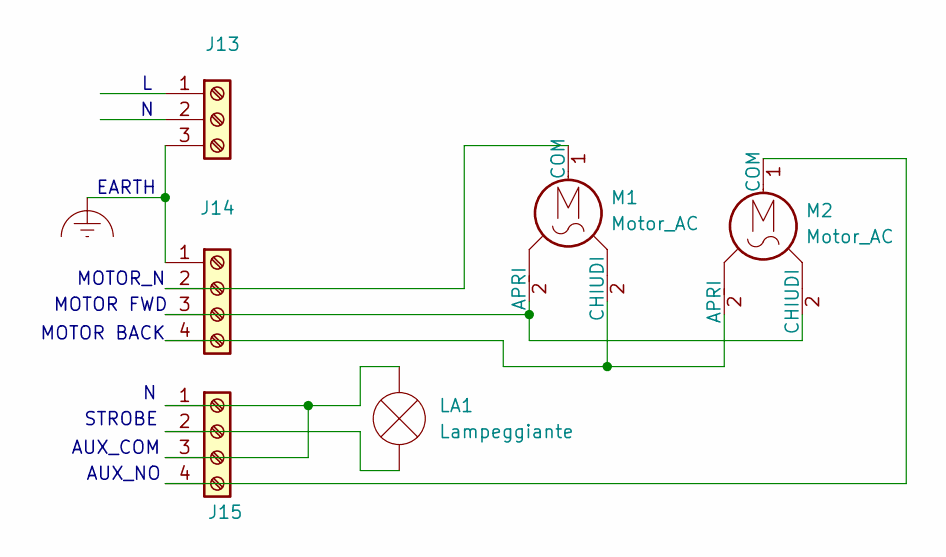
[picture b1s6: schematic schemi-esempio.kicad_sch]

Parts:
J13: Screw_Terminal_01x03; CONN-TH_3P-P5.00_WJ500V-5.08-3P
J14, J15: Screw_Terminal_01x04; CONN-TH_4P-P5.08_DIBO_DB128V-5.08
LA1: Lampeggiante
M1, M2: Motor_AC

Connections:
unnamed: J13.3, J14.1
unnamed: J14.2, M1.1 (COM)
unnamed: J14.3, M1.2 (APRI), M2.2 (APRI)
unnamed: J14.4, M1.2 (APRI), M2.2 (APRI)
unnamed: J15.1, J15.3, LA1.2 (+)
unnamed: J15.2, LA1.1 (-)
unnamed: J15.4, M2.1 (COM)

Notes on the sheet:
EARTH
AUX_NO
MOTOR FWD
MOTOR_N
STROBE
MOTOR BACK
AUX_COM
